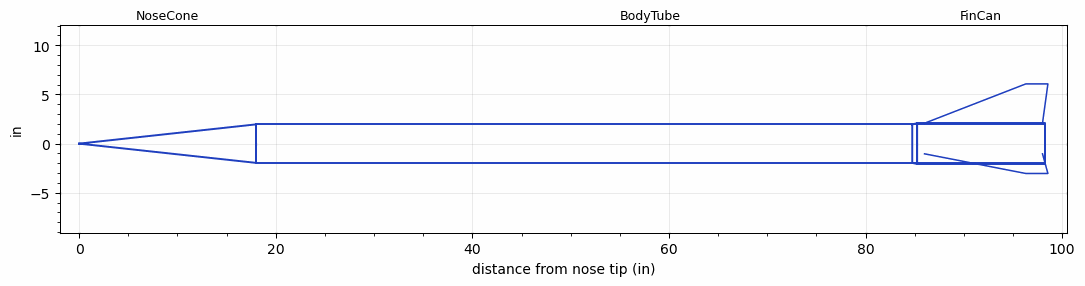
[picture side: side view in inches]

<RASAeroDocument>
 <FileVersion>2</FileVersion>
 <RocketDesign>
  <NoseCone>
   <Length>18</Length>
   <Diameter>3.9173</Diameter>
   <Shape>Conical</Shape>
   <BluntRadius>0.05</BluntRadius>
   <Location>0</Location>
  </NoseCone>
  <BodyTube>
   <Length>80.25</Length>
   <Diameter>3.9173</Diameter>
   <Location>18</Location>
  </BodyTube>
  <FinCan>
   <Length>13</Length>
   <Diameter>4.15</Diameter>
   <InsideDiameter>3.9173</InsideDiameter>
   <Location>98.25</Location>
   <ShoulderLength>0.5</ShoulderLength>
   <Offset>-13</Offset>
   <Fin>
    <Count>3</Count>
    <Chord>12</Chord>
    <Span>4</Span>
    <SweepDistance>10.3</SweepDistance>
    <TipChord>2.25</TipChord>
    <Thickness>0.189</Thickness>
    <LERadius>0.025</LERadius>
    <Location>12.25</Location>
    <AirfoilSection>Hexagonal</AirfoilSection>
    <FX1>1</FX1>
    <FX3>1</FX3>
   </Fin>
  </FinCan>
  <Surface>Smooth Paint</Surface>
  <ModifiedBarrowman>False</ModifiedBarrowman>
  <Turbulence>True</Turbulence>
  <SustainerNozzle>2.488</SustainerNozzle>
  <UseBooster1>False</UseBooster1>
  <UseBooster2>False</UseBooster2>
  <Comments>Don't Debate This N5800 Minimum Diameter Rocket
First N5800 Minimum Diameter Rocket to Survive and Not Shred
Mike Pasaretti
Black Rock Launch Site

Featherweight Barometric Altitude = 56504 ft
PerfectFlight Barometric Altitude = 56641 ft

Average of the Two Barometric Altitudes = 56573 ft

RASAero II Prediction = 61982 ft
Error = 9.56%
</Comments>
 </RocketDesign>
 <LaunchSite>
  <Altitude>3750</Altitude>
  <Pressure>0</Pressure>
  <RodAngle>2</RodAngle>
  <RodLength>10</RodLength>
  <Temperature>80</Temperature>
  <WindSpeed>5</WindSpeed>
 </LaunchSite>
 <Recovery>
  <Altitude1>1000</Altitude1>
  <Altitude2>2000</Altitude2>
  <DeviceType1>Parachute</DeviceType1>
  <DeviceType2>Parachute</DeviceType2>
  <Event1>True</Event1>
  <Event2>True</Event2>
  <Size1>24</Size1>
  <Size2>72</Size2>
  <EventType1>Apogee</EventType1>
  <EventType2>Altitude</EventType2>
  <CD1>1.33</CD1>
  <CD2>1.33</CD2>
 </Recovery>
 <MachAlt>
  <Item>0, 0</Item>
 </MachAlt>
 <SimulationList>
  <Simulation>
   <SustainerEngine>N5800-CS  (CTI)</SustainerEngine>
   <SustainerLaunchWt>48.19</SustainerLaunchWt>
   <SustainerNozzleDiameter>2.488</SustainerNozzleDiameter>
   <SustainerCG>64.69</SustainerCG>
   <SustainerIgnitionDelay>0</SustainerIgnitionDelay>
   <Booster1SeparationDelay>0</Booster1SeparationDelay>
   <Booster1IgnitionDelay>0</Booster1IgnitionDelay>
   <IncludeBooster1>False</IncludeBooster1>
   <Booster2Delay>0</Booster2Delay>
   <IncludeBooster2>False</IncludeBooster2>
   <TimetoApogee>55.48669</TimetoApogee>
   <MaxAltitude>61982.29</MaxAltitude>
   <MaxVelocity>3469.286</MaxVelocity>
  </Simulation>
 </SimulationList>
</RASAeroDocument>
